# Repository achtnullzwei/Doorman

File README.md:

<h1 align="center">
    <br>
    Doorman S3
    <br>
    <br>
    
    <br>
</h1>

**Doorman S3** is a versatile intercom gateway designed to connect your [TCS](https://www.tcsag.de/) or [Koch](https://www.kochag.ch/) intercom system to any home automation platform. It's also compatible with rebranded versions of [Niko](https://www.niko.eu/), [Scantron](https://scantron.dk/), and older [Jung](https://www.jung-group.com/) intercom models.

But that's not all - the **Doorman S3** is more than just an intercom bridge. With its integrated relay, you can simulate button presses to control door openers or lights, supporting up to **40V** and a maximum of **2.5A**. 

Even if your intercom system isn't directly listed, if it operates on a **2-wire bus** in the **14-24V DC range**, you may still be able to implement other protocols. Additionally, you can monitor voltage levels from older intercom systems to trigger actions based on those readings.

For more information on the manufacturing process, head to the **Manufacturing** section further down.

---

<div id="toc">
  <ul style="list-style: none">
    <summary>
      <h1>🚀 Getting started</h1>
    </summary>
  </ul>
</div>

Before diving into the installation process, visit the [Doorman Docs](https://doorman.azon.ai/) for comprehensive setup guides. If you have questions, don't hesitate to reach out on [Discord](https://discord.gg/t2d34dvmBf) or [GitHub Issues](https://github.com/azoninc/doorman/issues). I'm here to assist!

---

<div id="toc">
  <ul style="list-style: none">
    <summary>
      <h1>📦 Interested in buying one?</h1>
    </summary>
  </ul>
</div>

You can get fully assembled **Doorman S3** units with the **[Doorman Firmware](https://doorman.azon.ai/guide/firmware/installation)** pre-installed and ready for immediate integration into **Home Assistant**. 

For inquiries, please use [this page](https://doorman.azon.ai/order).

---

<div id="toc">
  <ul style="list-style: none">
    <summary>
      <h1>🛠️ Built Your Own Hardware?</h1>
    </summary>
  </ul>
</div>

Check out the [TC:BUS ESPHome component documentation](https://doorman.azon.ai/reference/esphome-component) for detailed instructions on integrating your DIY hardware with the TC:BUS. Whether you're expanding your **Doorman project** or using it as a starting point for your own system, this resource will guide you through seamless integration.

---

<div id="toc">
  <ul style="list-style: none">
    <summary>
      <h1>🤖 Features</h1>
    </summary>
  </ul>
</div>

- **ESP32-S3 Powered** for robust performance
- **USB-C port** for effortless flashing (because USB-C is just cool 😎)
- **Compact design** fits into any setup
- **Configurable WS2812B RGB LED** for event-based visual indicators
- **Two additional GPIOs** for easy expansion (e.g., I²C sensors)
- **Solid-state relay** for switching up to 40V (max. 2.5A)—perfect for older intercom systems
- **External Button** (G + BTN) for manual triggering
- **Bridge Rectifier** for correcting polarity on bus-wire input
- **TC:BUS Communication** for door functions and detecting the doorbell
- **Nuki Bridge functionality** with the [Nuki Bridge Addon](https://doorman.azon.ai/guide/firmware/nuki-bridge)

---

<div id="toc">
  <ul style="list-style: none">
    <summary>
      <h1>✔️ Compatibility</h1>
    </summary>
  </ul>
</div>

If your TCS or Koch intercom uses **screw terminals labeled `a`, `b`, and `P`** and operates on **24V DC**, it's most likely compatible with **Doorman**.

For more in-depth compatibility information, refer to the [Compatibility Docs](https://doorman.azon.ai/guide/hardware-compatibility).

---

<div id="toc">
  <ul style="list-style: none">
    <summary>
      <h1>🛠️ Manufacturing</h1>
    </summary>
  </ul>
</div>

A huge thanks to [PCBX](https://www.pcbx.com/?mtm_campaign=review&mtm_kwd=BD&mtm_source=flo) for manufacturing and sponsoring 10 awesome PCBs for this project! Your support means a lot to us, and your prices are seriously hard to beat. We're thrilled to have you on board!

If you're looking for a reliable PCB manufacturer for your own project, definitely check out [PCBX](https://www.pcbx.com/?mtm_campaign=review&mtm_kwd=BD&mtm_source=flo). While their production might take a little longer than some others, the unbeatable prices and super-easy part sourcing make it absolutely worth it. They handle everything for you!  

You can find all the necessary files for manufacturing the **Doorman S3** [here](https://github.com/azoninc/doorman/tree/master/pcb).

---

<div id="toc">
  <ul style="list-style: none">
    <summary>
      <h1>🙌 Contributing</h1>
    </summary>
  </ul>
</div>

To get started, check out our [Contributing Guidelines](CONTRIBUTING.md).

---

<div id="toc">
  <ul style="list-style: none">
    <summary>
      <h1>🚩 Repository Structure</h1>
    </summary>
  </ul>
</div>

The repository is organized as follows:
- **`blueprints`**: Automation Blueprints for Home Assistant
- **`components`**: External component files for ESPHome
- **`docs`**: Documentation
- **`enclosure`**: STL design files for the enclosure
- **`firmware`**: ESPHome configuration files
- **`pcb`**: KiCad schematic and PCB design files

---

<div id="toc">
  <ul style="list-style: none">
    <summary>
      <h1>📜 Credits</h1>
    </summary>
  </ul>
</div>

The **Doorman S3** project heavily relies on contributions from several key sources. Without their efforts, this project wouldn't be where it is today. ❤️

**[TCSIntercomArduino](https://github.com/atc1441/TCSintercomArduino)**\
Different Methods to read from and write to the TCS Bus.\
Feel free to watch the [Reverse Engineering Video](https://www.youtube.com/watch?v=xFLoauqj9yA) if you're interested.

**[tcs-monitor](https://github.com/Syralist/tcs-monitor)**\
An mqtt monitor for listening to the TCS Bus.\
You can find more information in this [Blog Post](https://blog.syralist.de/posts/smarthome/klingel/).

**[Doorman](https://github.com/peteh/doorman)**\
A lot of this Doorman project is based on peteh's one.\
The main goal is to provide a proper PCB for his Doorman Project.

**[ESPHome_nuki_lock](https://github.com/uriyacovy/ESPHome_nuki_lock)**\
This module builds an ESPHome lock platform for Nuki Smartlock (nuki_lock).

**[AStrehlau](https://github.com/AStrehlau)**\
Thank you so much for your time, patience, expertise, and every piece of invaluable advice that helped make this project better, smaller, and more affordable.

**[calibanorg](https://github.com/calibanorg)**\
Thank you so much for your support, both in terms of encouragement and financial assistance, in the development of Doorman.

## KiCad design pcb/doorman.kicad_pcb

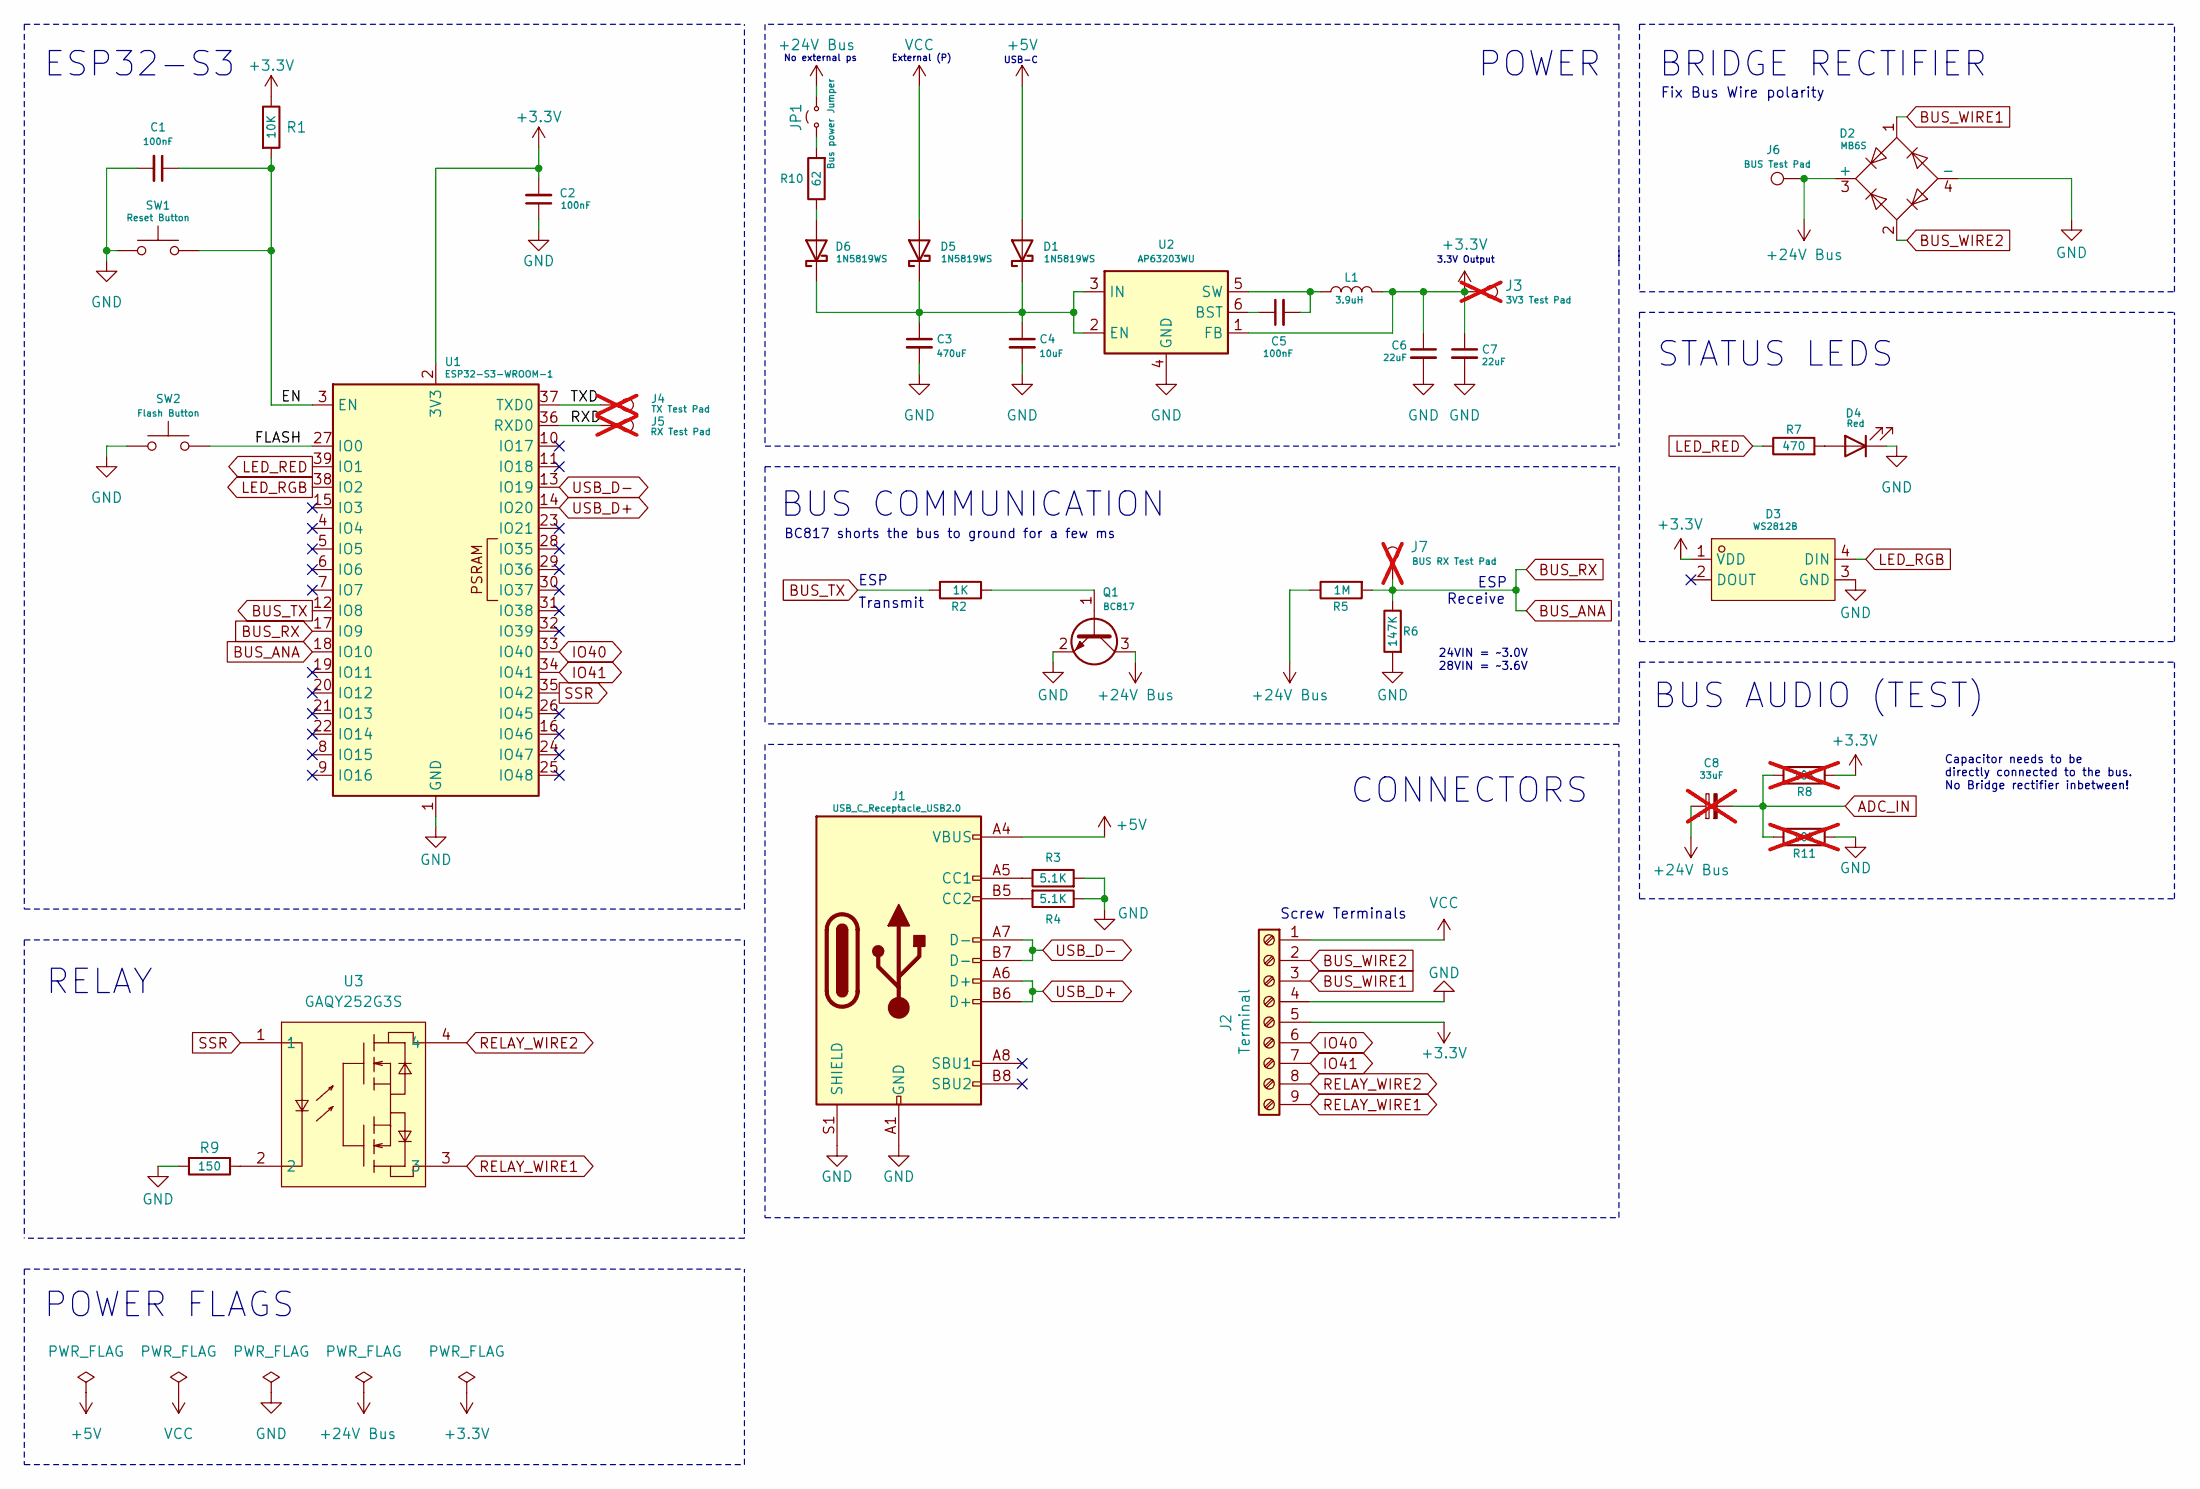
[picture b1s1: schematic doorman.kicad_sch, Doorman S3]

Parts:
C1, C2, C5: 100nF; C_0603_1608Metric; MPN CC0603KRX7R9BB104; LCSC C14663
C3: 470uF; CP_Elec_8x10; MPN 189RV0027; LCSC C7471889
C4: 10uF; C_1206_3216Metric; MPN CL31A106KBHNNNE; LCSC C13585
C6, C7: 22uF; C_0603_1608Metric; MPN CL10A226MQ8NRNC; LCSC C59461
C8: 33uF; not fitted
D1, D5, D6: 1N5819WS; D_SOD-323; MPN 1N5819WS; LCSC C191023
D2: MB6S; TO-269AA; MPN MB6S; LCSC C2886734
D3: WS2812B; LED-SMD_4P-L2.0-W1.8_CY-0807; MPN XL-0807RGBC-WS2812B-S; LCSC C41413181
D4: Red; LED_0603_1608Metric; MPN XL-1608SURC-06; LCSC C965799
J1: USB_C_Receptacle_USB2.0; USB_C_Receptacle_HRO_TYPE-C-31-M-12; MPN TYPE-C 16PIN 2MD(073); LCSC C2765186
J2: Terminal; CONN-TH_9P-P2.54_KF128-2.54-9P; MPN DB125-2.54-9P-GN-S; LCSC C918127
J3: 3V3 Test Pad; TestPoint_Pad_D1.0mm; not fitted
J4: TX Test Pad; TestPoint_Pad_D1.0mm; not fitted
J5: RX Test Pad; TestPoint_Pad_D1.0mm; not fitted
J6: BUS Test Pad; TestPoint_Pad_D1.0mm
J7: BUS RX Test Pad; TestPoint_Pad_D1.0mm; not fitted
JP1: Bus power Jumper; PinHeader_1x02_P1.27mm_Vertical; MPN DZ127R-11-02-25; LCSC C2935942
L1: 3.9uH; L_Abracon_ASPI-4030S; MPN SWPA4030S3R9MT; LCSC C96899
Q1: BC817; SOT-23; MPN BC817-25; LCSC C5184412
R1: 10K; R_0603_1608Metric; MPN 0603WAF1002T5E; LCSC C25804
R2: 1K; R_0402_1005Metric; MPN 0402WGF1001TCE; LCSC C11702
R3, R4: 5.1K; R_0402_1005Metric; MPN 0402WGF5101TCE; LCSC C25905
R5: 1M; R_0603_1608Metric; MPN 0603WAF1004T5E; LCSC C22935
R6: 147K; R_0603_1608Metric; MPN 0603WAF1473T5E; LCSC C22878
R7: 470; R_0603_1608Metric; MPN 0603WAF4700T5E; LCSC C23179
R8, R11: 10K; R_0603_1608Metric; MPN 0603WAF1002T5E; LCSC C25804; not fitted
R9: 150; R_0402_1005Metric; MPN 0402WGF1500TCE; LCSC C25082
R10: 62; R_1206_3216Metric; MPN 1206W4F620JT5E; LCSC C17971
SW1: Reset Button; SW_SPST_B3U-1000P-B; MPN HX-B3U-1000P-1.6N; LCSC C49234121
SW2: Flash Button; SW_SPST_B3U-1000P-B; MPN HX-B3U-1000P-1.6N; LCSC C49234121
U1: ESP32-S3-WROOM-1; MPN ESP32-S3-WROOM-1-N8R8; LCSC C2913201
U2: AP63203WU; TSOT-23-6; MPN AP63203WU-7; LCSC C780769
U3: GAQY252G3S; SOP-4_L4.4-W4.0-P2.54-LS7.0-TL; MPN GAQY252G3S; LCSC C7435106

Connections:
+3.3V: C2.2, C6.1, C7.1, D3.1 (VDD), J2.5, J3.1, J3.5, L1.2, R1.1, R8.1, U1.2 (3V3), U2.1 (FB)
+5V: D1.2 (A), J1.A4 (VBUS), J1.A9 (VBUS), J1.B4 (VBUS), J1.B9 (VBUS)
+24V Bus: D2.3 (+), J6.1, JP1.2 (B), Q1.3 (C), R5.1
/EN: C1.1, R1.2, SW1.1, U1.3 (EN)
/FLASH: SW2.1, U1.27 (IO0)
/RXD: J5.1, U1.36 (RXD0)
/TXD: J4.1, U1.37 (TXD0)
BUS_ANA: J7.1, R5.2, R6.1, U1.17 (IO9), U1.18 (IO10)
BUS_TX: R2.2, U1.12 (IO8)
BUS_WIRE1: D2.1, J2.3
BUS_WIRE2: D2.2, J2.2
GND: C1.2, C2.1, C3.2, C4.2, C6.2, C7.2, D2.4 (-), D3.3 (GND), D4.1 (K), J1.A1 (GND), J1.A12 (GND), J1.B1 (GND), J1.B12 (GND), J1.S1 (SHIELD), J2.4, J3.4, Q1.2 (E), R3.2, R4.1, R6.2, R9.2, R11.1, SW1.2, SW2.2, U1.1 (GND), U1.40 (GND), U1.41 (GND), U2.4 (GND)
IO40: J2.6, U1.33 (IO40)
IO41: J2.7, U1.34 (IO41)
LED_RED: R7.1, U1.39 (IO1)
LED_RGB: D3.4 (DIN), U1.38 (IO2)
unnamed: C8.2, R8.2, R11.2
unnamed: C3.1, C4.1, D1.1 (K), D5.1 (K), D6.1 (K), U2.2 (EN), U2.3 (IN)
unnamed: D4.2 (A), R7.2
unnamed: D6.2 (A), R10.1
unnamed: J1.A5 (CC1), R3.1
unnamed: J1.B5 (CC2), R4.2
unnamed: JP1.1 (A), R10.2
unnamed: Q1.1 (B), R2.1
unnamed: R9.1, U3.2
unnamed: C5.1, U2.6 (BST)
unnamed: C5.2, L1.1, U2.5 (SW)
RELAY_WIRE1: J2.9, U3.3
RELAY_WIRE2: J2.8, U3.4
SSR: U1.35 (IO42), U3.1
USB_D+: J1.A6 (D+), J1.B6 (D+), U1.14 (IO20)
USB_D-: J1.A7 (D-), J1.B7 (D-), U1.13 (IO19)
VCC: D5.2 (A), J2.1

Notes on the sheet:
Screw Terminals
USB-C
No external ps
BUS AUDIO (TEST)
ESP
Capacitor needs to be directly connected to the bus. No Bridge rectifier inbetween!
POWER
24VIN = ~3.0V 28VIN = ~3.6V
Transmit
CONNECTORS
3.3V Output
STATUS LEDS
External (P)
ESP32-S3
Fix Bus Wire polarity
RELAY
BRIDGE RECTIFIER
BC817 shorts the bus to ground for a few ms
POWER FLAGS
Receive
BUS COMMUNICATION

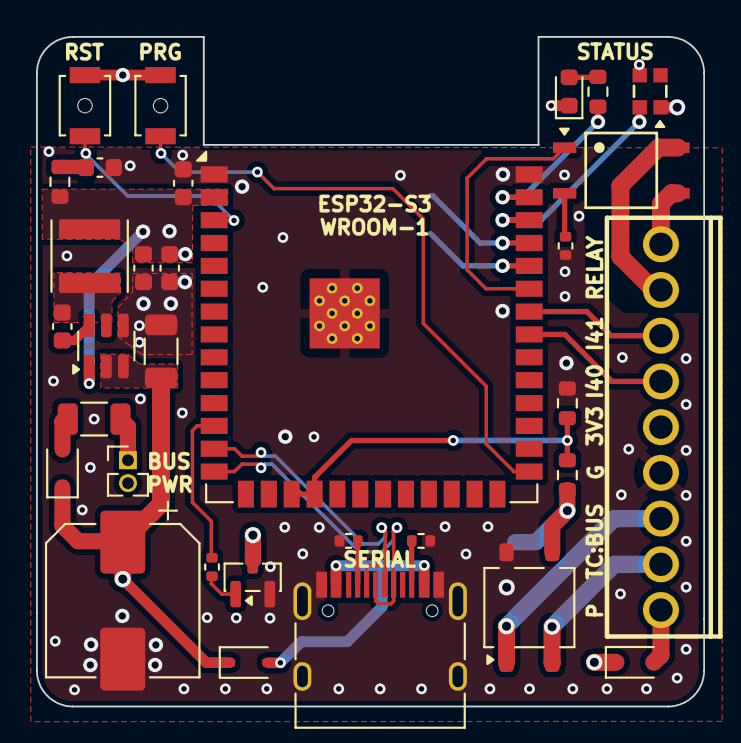
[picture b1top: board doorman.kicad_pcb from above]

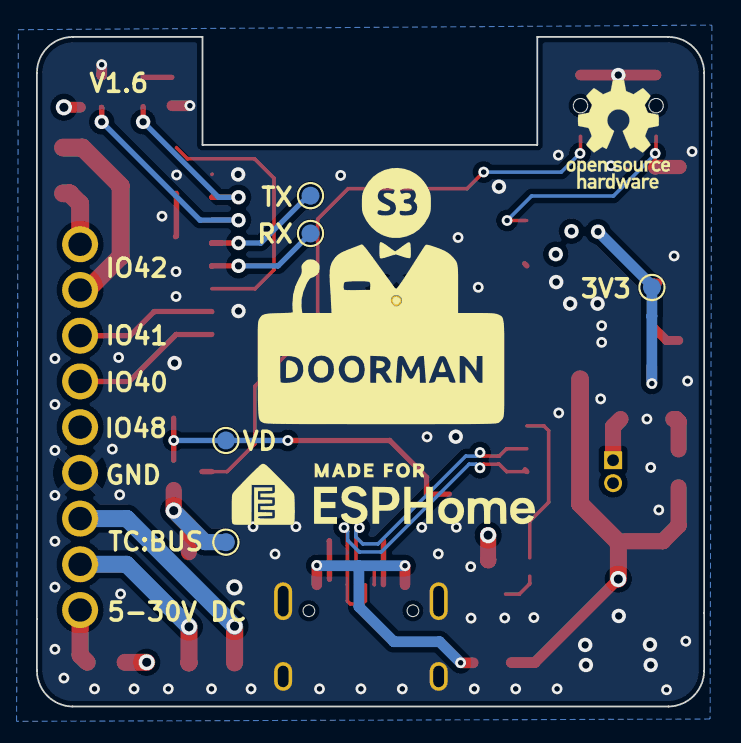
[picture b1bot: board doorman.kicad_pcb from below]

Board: 4 copper layers, 37.1 x 37.2 mm, 37 parts (5 on the bottom side), 32 nets.

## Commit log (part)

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2025-05-28 Set RTO Timeout script mode to restart
2025-05-28 Adjust changelog headings in CI
2025-05-28 Remove 300ms delay from apartment doorbell RTO
2025-05-28 Update Docs
2025-05-28 Show bus activity via status led
2025-06-03 Remove ESP8266 builds
2025-06-03 Add HomeKit API variant
2025-06-03 Build Homekit variants
2025-06-04 Fix Homekit FW builds
2025-06-04 Add HomeKit docs
2025-06-04 Use correct homekit branch
2025-06-04 Update HomeKit Docs
2025-06-04 Use Light Entity instead of Button
2025-06-04 Update Changelog
2025-06-07 Refactor and extend HomeKit components
2025-06-11 Refactor HomeKit components
2025-06-11 Experimental Doorbell supression
2025-06-11 HomeKit Bridge refactor
2025-06-11 Test lib change
2025-06-11 Extend Doorbell Accessory
2025-06-11 Refactor
2025-06-11 Add identify callbacks
2025-06-11 Replace doorbelll uuid with define
2025-06-11 Remove Doorbell Supression
2025-06-12 Effect Test
2025-06-12 Update effects
2025-06-12 Dont set brightness on effect
2025-06-12 change effect
2025-06-12 set default transition length
2025-06-12 WIP Order Page
2025-06-12 Update references
2025-06-13 Add payment options
2025-06-16 Add ISH1030 identifier variant
2025-06-16 Tests
2025-06-16 Debug Logging
2025-06-16 Fix log
2025-06-16 Rebuild command data if modified
2025-06-16 fix bit logic
2025-06-16 Fix command builder sn bug
2025-06-16 intercom-settings.yaml: consistent wording "Indoor Station"
    Both the settings UI and the Quickstart guide generally use "Indoor Station", as opposed to "Intercom". Let's use consistent wording here.
2025-06-16 Fix door protocol override
2025-06-16 Fix door call parser
2025-06-16 Add Door Opener Mode Setting
2025-06-16 Extend request_version to cover other device groups as well
2025-06-16 Fix logic
2025-06-16 Implement identification for other device groups
2025-06-16 Fix conditions
2025-06-16 Add support for a few control units
2025-06-16 Extend discovery to controllers
2025-06-16 Add BVS20
2025-06-16 Refactor discovery
2025-06-16 Add Debug Models
2025-06-17 Individual Debug Log Levels - tc_bus
2025-06-17 Add new is_response flag
2025-06-17 Fixes
2025-06-17 Rename telegram property to raw
2025-06-17 Adjust timings
2025-06-17 send all telegrams to remote listener
2025-06-18 Improve logging
2025-06-18 Add missing is_data member
2025-06-18 Add receive flag to on_receive
2025-06-18 Activate model identification by telegram type
2025-06-18 Fix identify model flow
2025-06-18 Failsafe memory reading flow
2025-06-18 Create configurations and examples for local development
2025-06-18 Add debug utils to local version
2025-06-19 Log RTO action execution
2025-06-24 Update Docs, add configo base component
2025-06-24 Enable pulldown on remote receiver
2025-08-31 WIP II
2025-08-31 Use Indoor Station instead of Intercom
2025-08-31 Separate Hardware Version Sensor and TC:Bus
2025-08-31 WIP: Sub Devices
2025-08-31 Consolidate files
2025-08-31 Split TC Bus Device WIP
2025-08-31 WIP III
2025-08-31 Fix string conversion
2025-09-01 Fix Homekit
2025-09-29 WIP: Order Form
2025-09-29 Patch Workflow
2025-09-29 Allow using cookies for cors
2025-09-29 WIP orders
2025-09-29 WIP order
2025-10-03 WIP order - move payment method
2025-10-07 Add new API Guards
2025-10-08 WIP order management
2025-10-08 Remove obsolete deps
2025-10-09 Update confirmable open door notification blueprint to not trigger from unavailable state (#60)
    * Update confirmable open door notification blueprint to not trigger from unavailable state
    ---------
2025-10-09 Bump version
2025-10-09 Test WF
2025-10-09 Add pagination to order list
2025-10-10 Fix links
2025-10-11 Update captive_portal
2025-10-11 Update Build actions
2025-10-11 Consolidate configuation options
2025-10-11 Update nuki lock component commit
2025-10-11 Cleanup component
2025-10-11 Cleanup
2025-10-14 Fix Setup mode for non default addresses
2025-10-14 Order: Integrate NIIMBOT label printer
2025-10-14 Order: Add status filter
2025-10-14 Bump min ESPHome version
2025-10-16 Disable events by default
2025-10-16 Update nuki bridge commit
2025-10-16 Reduce homekit memory
2025-10-16 Reduce doorman hardware memory
2025-10-16 MQTT: Publish parsed telegrams
2025-10-16 Docs: Correct mqtt command topic
2025-10-17 Docs: Change Modal Style
2025-10-18 Simplify build process
2025-10-18 Cleanup CI
2025-10-18 Docs: Add missing Nuki Bridge config
2025-10-19 Docs: Add missing device button information
2025-10-19 CI: Build all variants as nightly
2025-10-19 Docs: Add RTO note
2025-10-19 Fix custom webserver include
2025-10-20 CI: Build webserver bundle
2025-10-20 CI: Fix webserver build
2025-10-20 CI: wait for webserver build before building firmware
2025-10-20 CI: Fix webserver upload
2025-10-20 Webserver: use static base64 img
2025-10-20 Webserver: Show all button after each group
2025-10-20 Add setup status sensors
2025-10-20 Fix c&p
2025-10-20 Improve setup mode logs
2025-10-20 Webserver: Fix margin
2025-10-20 Webserver: Fix input width
2025-10-20 Webserver: Change range input styling
2025-10-20 Webserver: Apply Doorman theme
2025-10-20 Webserver: Current Firmware version in title
2025-10-20 Webserver: Fix width
2025-10-21 Docs: Streamline improv wifi/bluetooth and web tools style
2025-10-21 Webserver: Add docs links
2025-10-21 Disable Relay Entity by default
2025-10-21 Use webserver dev branch for dev
2025-10-21 Webserver: Change texts
2025-10-21 Webserver: Change Hardware detection
2025-10-21 Fix wrong webserver js on local builds
2025-10-21 Docs: Add web ui setup info
2025-10-21 Webserver: Show more setup details
2025-10-21 Turn on setup mode on boot if serial number is missing
2025-10-21 Webserver: Change icon
2025-10-21 Webserver: Change connected icon
2025-10-21 Webserver: Rename OPN to Open
2025-10-22 Webserver: Remove ESPHome version
2025-10-22 Disable less frequently used entities by default
2025-10-23 Fix Nuki component
2025-10-23 Log correct values for outdoor station settings
2025-10-23 Docs: Update Outdoor Station section
2025-10-23 Fix name duplication
2025-10-24 Add methods to interface outdoor station button config
2025-10-28 Update CI Workflows
2025-10-28 Fix Nuki Builds
2025-10-28 Switch back to nuki main branch
2025-10-30 Update pcb files
2025-11-05 Docs: Use dayjs instead of momentjs
2025-11-05 Switch to current_option()
2025-11-05 Migrate automation actions
2025-11-05 Migrate automation conditions
2025-11-05 Code cleanup
2025-11-05 Fix classname
2025-11-10 Docs: Order wording
2025-11-10 Change Doorman-S3 name
2025-11-10 Add TinyUSB
2025-11-10 Docs: New order status
2025-11-10 Docs: Update API
2025-11-10 docs(order): Add tracking buttons
2025-11-10 chore: Add scope
2025-11-11 docs(order): Prevent multiple requests
2025-11-11 refactor: Code cleanup
2025-11-11 docs(changelog): Fix format
2025-11-11 docs: Fix wrong reference
2025-11-11 docs: Show github contributors on creators page
2025-11-12 fix: Fix missing color mode
2025-11-13 refactor: Add debug logs
2025-11-24 refactor: Rename Condition Schema
2025-11-24 build: Change Stock Firmware Name
2025-11-24 style: Change package name in minimal examples
2025-11-24 build: Use jq to change manifest values
2025-11-24 build: Add integration name to manifest
2025-11-24 docs: Fix page description generator
2025-11-24 chore: Add render files
2025-11-24 chore: Change readme logo
2025-11-27 refactor: Remove old code
2025-11-27 feat: Compatibility with new nuki smart lock generations
2025-11-27 fix: Fix potential issues when requesting the version multiple times
2025-11-27 feat: Allow user to set encryption key via HA
2025-11-27 fix: Fix api encryption key
2025-11-27 refactor: Use info level for some important things
2025-11-27 refactor: Disable second door lock if address not set
2025-11-27 fix: Remove default nuki pin
2025-11-27 fix: Use state subscription api clients to show status
2025-11-27 refactor: Mark second door entities internal on boot if address is unset
2025-11-27 refactor: Use HA encryption key
2025-11-27 fix: Avoid confusion with setup info entities by adding prefix
2025-11-27 fix: Fix Doorman Hardware Version component
2025-11-27 refactor: Migrate get_device_class
2025-11-27 fix: Fix incomplete code
2025-11-27 fix: Fix homekit setup log
2025-11-30 refactor: Enable Nuki Pairing Mode and Pin by default
2025-11-30 feat: Add new Nuki settings
2025-11-30 refactor: Set indoor station settings internal if not available
2025-12-01 refactor: Dump memory buffer after reading (idf debug)
2025-12-01 refactor: Use Log Level Entity instead of substitution
2025-12-01 feat: Show AP state via RGB status LED
2025-12-01 refactor: Categorize Nuki Settings
2025-12-01 style: Change web UI debug log text color
2025-12-01 refactor: Optimize function to hide unavailable entities
2025-12-01 refactor: Disable remote.raw log level lower or equal 3
2025-12-01 style: Cleanup
2025-12-01 feat: Add open trait to lock
2025-12-01 fix: Fix tc_bus components priority
2025-12-01 refactor: Conditionally log device settings
2025-12-01 fix: Update setup mode properly on address changes
2025-12-02 refactor: Use multiline logs
2025-12-02 refactor: Set lower log levels
2025-12-02 fix: Fix webserver multiline
2025-12-02 docs: Update Changelog
2025-12-02 docs: Add setup details image
2025-12-02 revert: Revert api encryption due to nuki issues
2025-12-02 style: Change Nuki sorting groups and order
2025-12-02 chore: Bump version
2025-12-02 docs: Prepare for rev 1.6
2025-12-03 refactor: Change setup prio
2025-12-03 Change nuki setup prio
2025-12-06 refactor: Use nuki-task branch
2025-12-06 fix: Fix homekit lights
2025-12-06 refactor: Check if desired state is already true
2025-12-07 feat: Implement automatic device identification and memory reading per device
2025-12-07 feat: Add auto_configuration option
2025-12-07 fix: Fix homekit light
2025-12-08 docs: Change shipping methods
2025-12-08 refactor: Improve Logs
2025-12-08 fix: Fix Log Format
2025-12-12 docs: Update Nuki Bridge docs
2025-12-12 refactor: Wait for wifi after disabling AP
2025-12-12 fix: Fix force_long_door_opener_protocol option name
2025-12-13 refactor: Rename Doorman hardware component to hardware and extend product name
2025-12-14 refactor: Adjust web UI
2025-12-14 fix: Fix Logging & Serial Number change detection
2025-12-14 fix: Fix model log
2025-12-15 fix: Fix set_internal logic
2025-12-15 refactor: Read memory after changing serial number
2025-12-15 fix: Fix DND log
2025-12-15 feat: Add Ringtone Mute Switch
2025-12-15 refactor: Cleanup tc_bus_device component
2025-12-15 fix: Fix supports_setting logic
2025-12-15 refactor: Change product to model
2025-12-15 docs: Update intercom settings docs
2025-12-15 refactor: Save model to efuse if not available (for previous batches)
2025-12-15 docs(order): Print labels in german as well
2025-12-15 refactor: Change Doorman Model & Revision sensors
2025-12-15 refactor: Improve hardware component
2025-12-15 refactor: Improve Logging
2025-12-15 fix: Add delay to select memory page to reduce false readings
2025-12-26 docs(order): Change texts
2025-12-27 docs: Add page descriptions
2025-12-27 docs: Add description property
2025-12-28 docs: Fix edit link
2025-12-31 feat: Add actions to reconfigure WiFi
2026-01-01 build: Temporary generate stock files
2026-01-02 docs(order): Use wide order page layout
2026-01-02 refactor: Add support for new entity urls
2026-01-03 refactor: Migrate to is_esp32
2026-01-07 refactor: Merge models based on product family
2026-01-09 docs(order): Improve order
2026-01-09 refactor: Fix SENSO PRO ringtone settings
2026-01-09 fix: Remove unavailable capabilities
2026-01-09 refactor: Cleanup models
2026-01-15 refactor: Cleanup arduino references
2026-01-18 build: Build captive portal index
2026-01-18 fix: Display connecting message
2026-01-19 refactor: Show Text instead of MAC
2026-01-19 docs: Update AP images
2026-01-20 docs(order): Change text
2026-01-20 fix: Fix Webserver Update check
2026-01-21 feat: Show version on webui update button
2026-01-21 docs: Update dependencies and fix manifest check
2026-01-21 chore: Update PCB schematic and BOM
2026-01-21 refactor: Adjust Entity names for new naming scheme
2026-01-21 fix: Fix RTO LED effect
2026-01-21 docs(order): Add country descriptions
2026-01-21 PCB WIP
2026-01-22 fix: Fix invalid host config
2026-01-22 refactor: Increase Log size
2026-01-22 fix: Fix telegram start duration
